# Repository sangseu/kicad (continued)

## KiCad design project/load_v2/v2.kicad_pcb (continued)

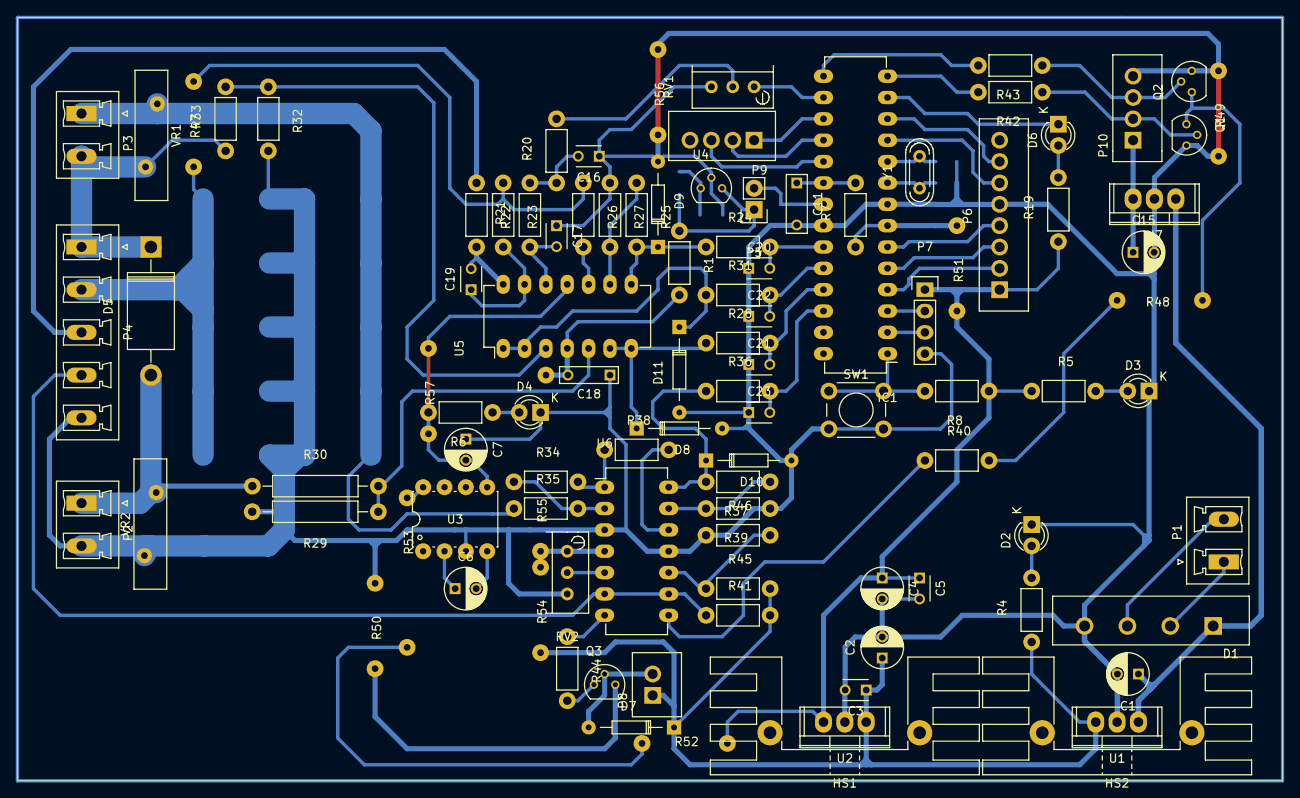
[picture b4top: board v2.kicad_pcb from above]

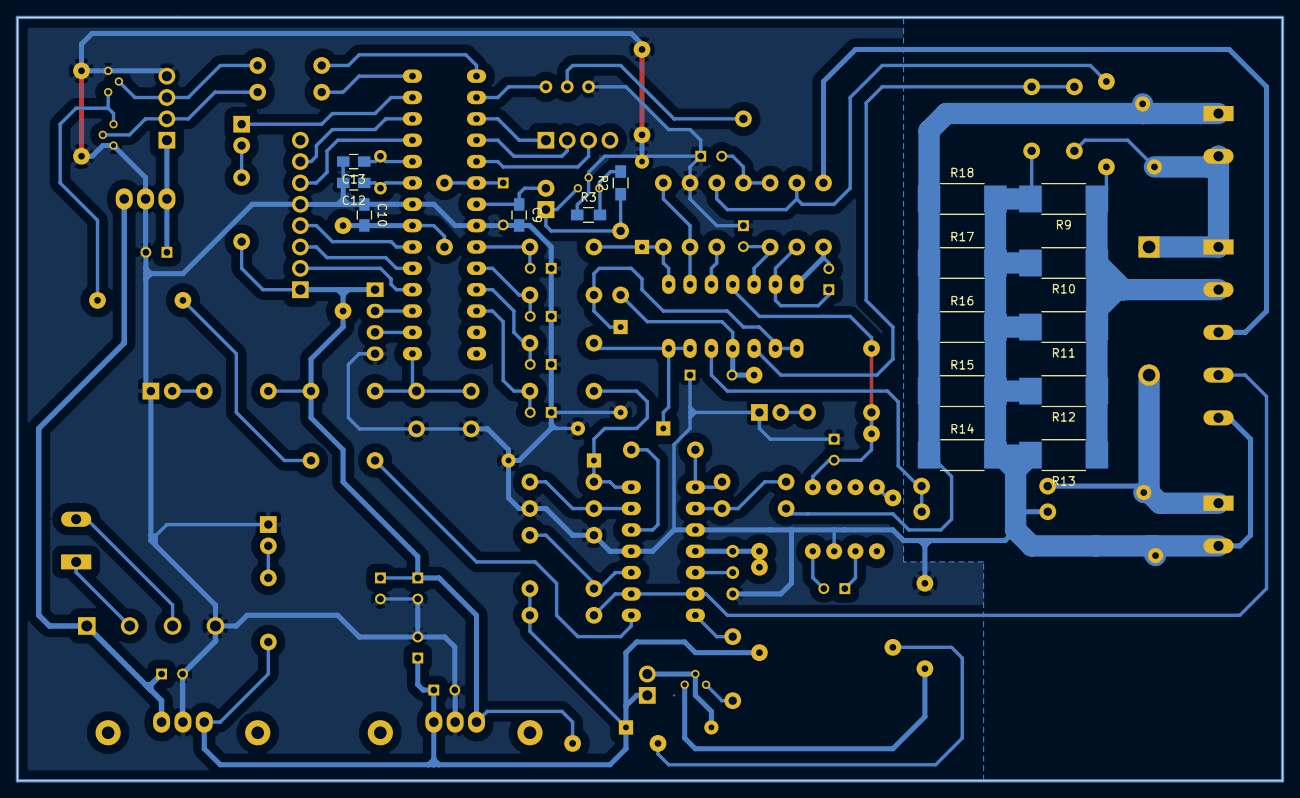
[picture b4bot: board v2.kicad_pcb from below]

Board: 2 copper layers, 150.5 x 90.8 mm, 118 parts (16 on the bottom side), 79 nets.

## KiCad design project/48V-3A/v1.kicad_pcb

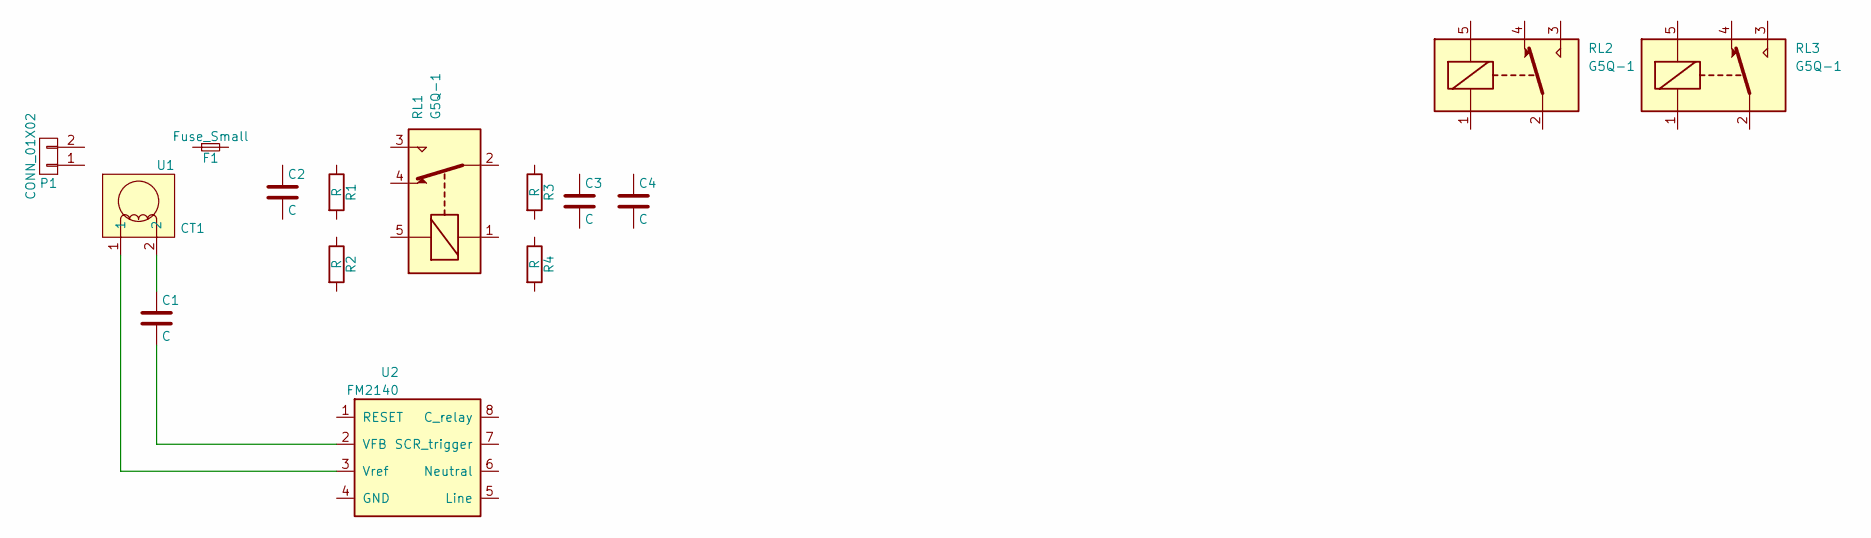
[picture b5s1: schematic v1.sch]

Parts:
C1: C; C_0805_HandSoldering
C2: C; C_Rect_L13_W6_H12_P10
C3, C4: C; C_Rect_L18_W5_P15
F1: Fuse_Small; CP4
P1: CONN_01X02; bornier2
R1, R2, R3, R4: R; R_0805_HandSoldering
RL1, RL2, RL3: G5Q-1; Relay_SANYOU_SRD_Series_Form_C
U1: CT1
U2: FM2140; SOIC-8_3.9x4.9mm_Pitch1.27mm

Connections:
unnamed: C1.1, U1.2
unnamed: C1.2, U2.2 (VFB)
unnamed: U1.1, U2.3 (Vref)

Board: 2 copper layers, 15 parts (0 on the bottom side), 3 nets, no tracks yet.

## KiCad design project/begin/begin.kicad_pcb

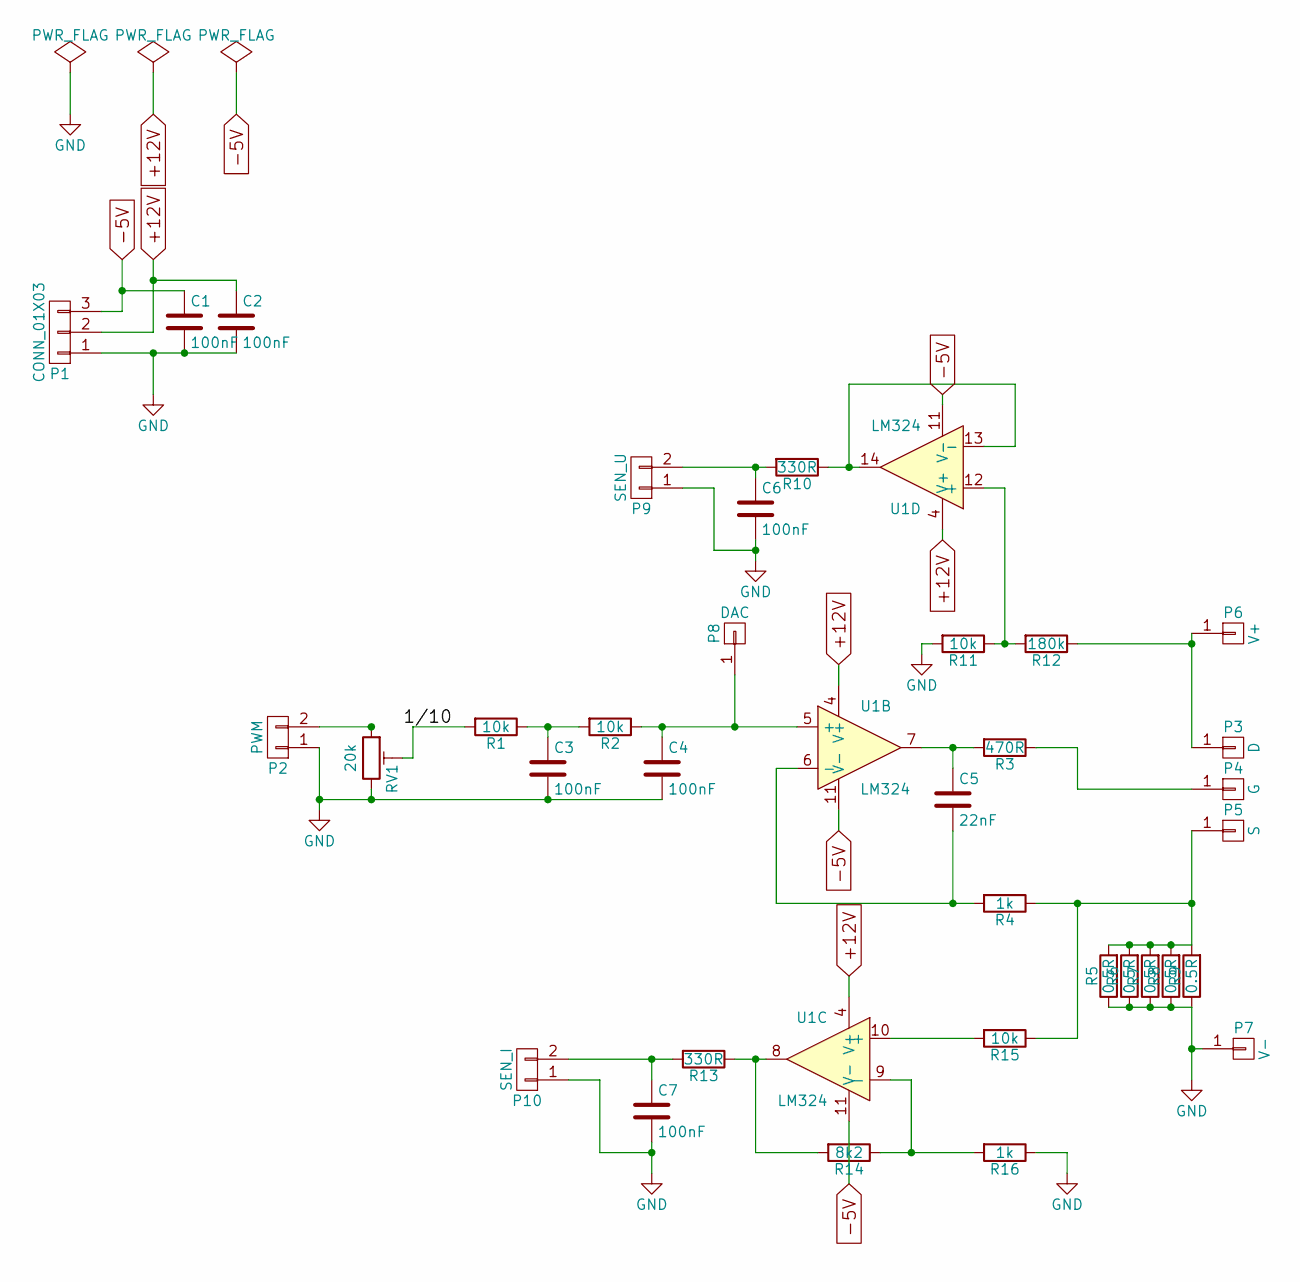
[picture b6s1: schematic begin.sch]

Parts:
C1: 100nF; C_Rect_L7_W2.5_P5
C2, C3, C4, C6, C7: 100nF; C_Disc_D3_P2.5
C5: 22nF; C_Disc_D3_P2.5
P1: CONN_01X03; Socket_Strip_Straight_1x03
P2: PWM; Socket_Strip_Straight_1x02
P3: D; SolderWirePad_single_2mmDrill
P4: G; SolderWirePad_single_2mmDrill
P5: S; SolderWirePad_single_2mmDrill
P6: V+; SolderWirePad_single_2mmDrill
P7: V-; SolderWirePad_single_2mmDrill
P8: DAC; Pin_Header_Straight_1x01
P9: SEN_U; Socket_Strip_Straight_1x02
P10: SEN_I; Socket_Strip_Straight_1x02
R1, R2, R11, R15: 10k; Resistor_Horizontal_RM7mm
R3: 470R; Resistor_Horizontal_RM7mm
R4, R16: 1k; Resistor_Horizontal_RM7mm
R5, R6, R7, R8, R9: 0.5R; R_2512_HandSoldering
R10, R13: 330R; Resistor_Horizontal_RM7mm
R12: 180k; Resistor_Horizontal_RM7mm
R14: 8k2; Resistor_Horizontal_RM7mm
RV1: 20k; PINHEAD1-3
U1: LM324; DIP-14_W7.62mm_LongPads

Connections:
+12V: C2.1, P1.2, U1.4 (V+)
-5V: C1.1, P1.3, U1.11 (V-)
GND: C1.2, C2.2, C3.2, C4.2, C6.2, C7.2, P1.1, P2.1, P7.1, P9.1, P10.1, R5.1, R6.1, R7.1, R8.1, R9.1, R11.2, R16.1, RV1.3
unnamed: C3.1, R1.1, R2.2
unnamed: C4.1, P8.1, R2.1, U1.5 (+)
unnamed: C5.1, R3.2, U1.7
unnamed: C5.2, R4.2, U1.6 (-)
unnamed: C6.1, P9.2, R10.2
unnamed: C7.1, P10.2, R13.2
unnamed: P2.2, RV1.1
unnamed: P3.1, P6.1, R12.1
unnamed: P4.1, R3.1
unnamed: P5.1, R4.1, R5.2, R6.2, R7.2, R8.2, R9.2, R15.1
unnamed: R1.2, RV1.2
unnamed: R10.1, U1.13 (-), U1.14
unnamed: R11.1, R12.2, U1.12 (+)
unnamed: R13.1, R14.2, U1.8
unnamed: R14.1, R16.2, U1.9 (-)
unnamed: R15.2, U1.10 (+)

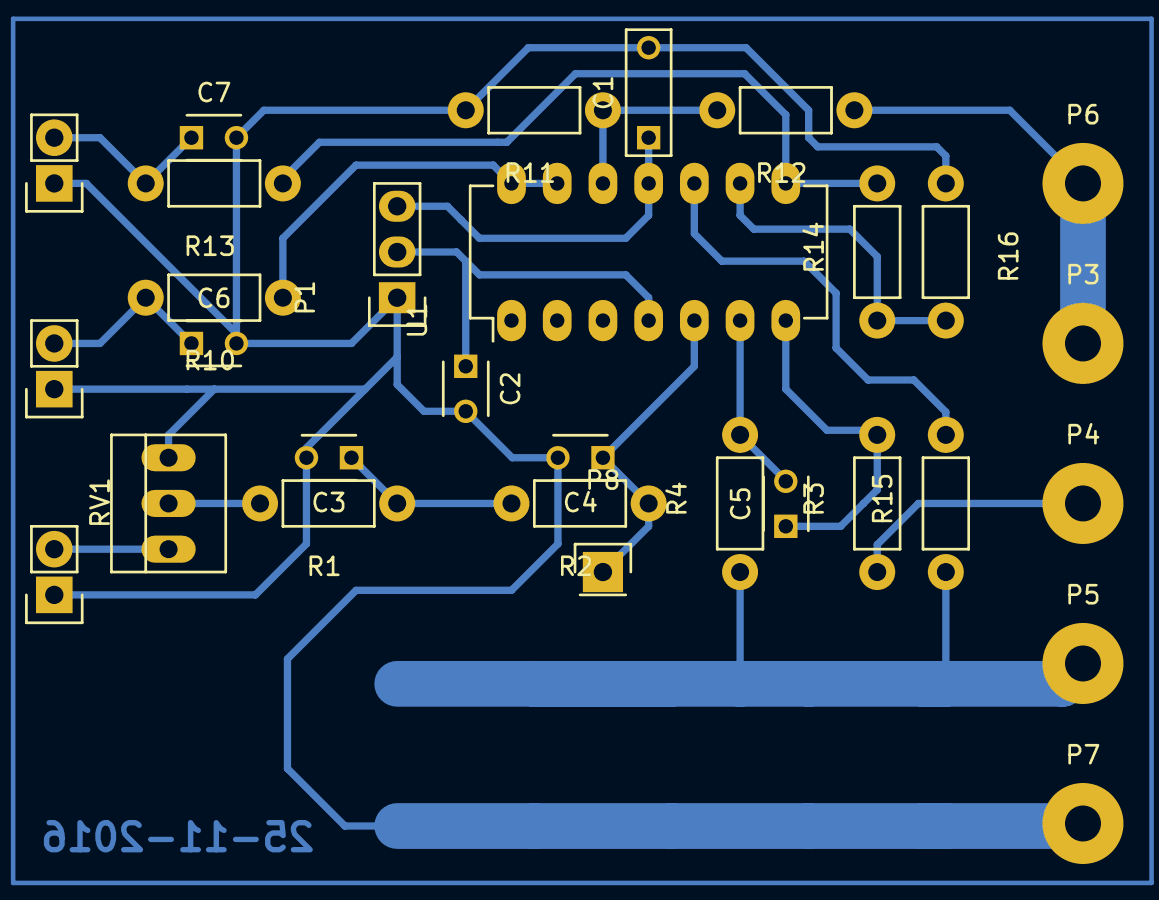
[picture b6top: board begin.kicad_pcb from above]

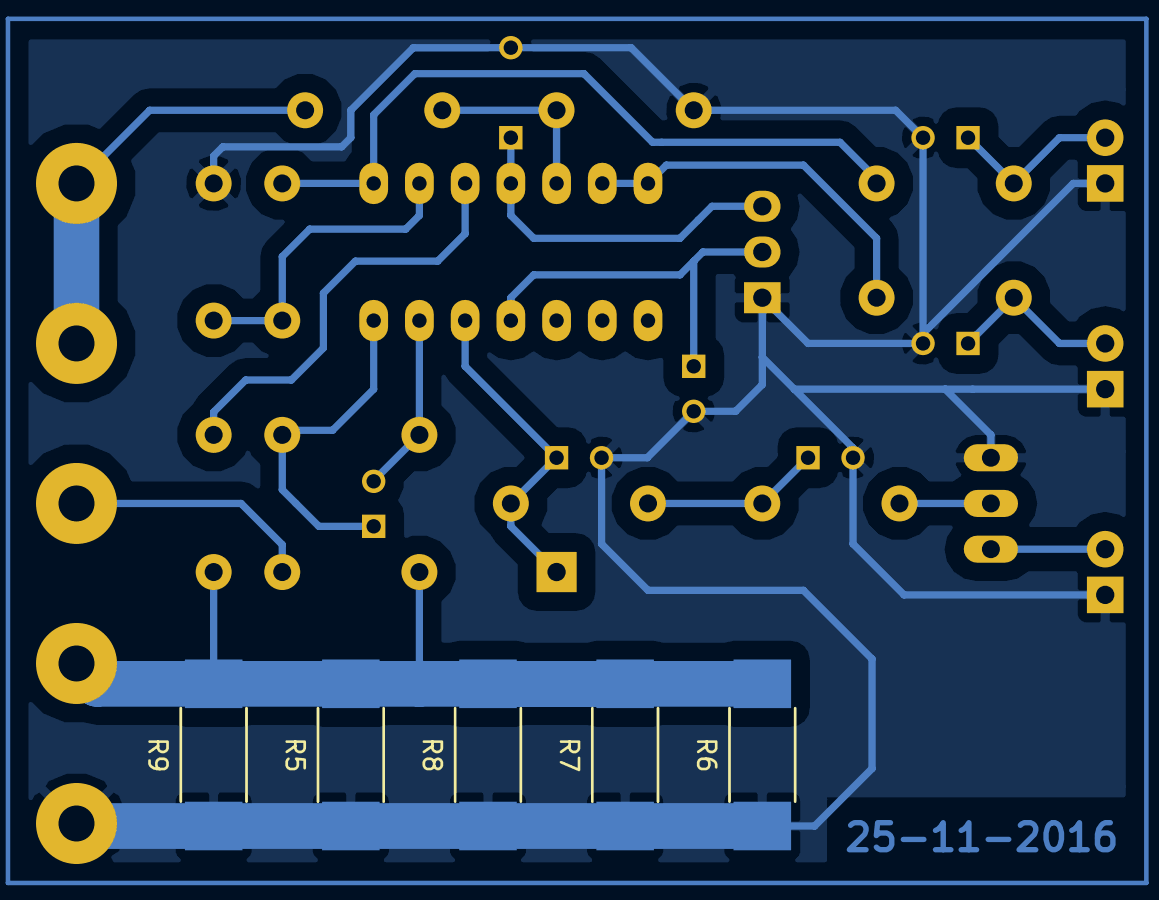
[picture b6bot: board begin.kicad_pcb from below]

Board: 2 copper layers, 35 parts (5 on the bottom side), 19 nets.

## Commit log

2016-11-28 creat
2016-11-29 schema_load_v2
2016-12-30 3fet
2016-12-30 chser
2017-05-30 chager
